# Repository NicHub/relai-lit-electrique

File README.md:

**Relai pour lit électrique**
=============================

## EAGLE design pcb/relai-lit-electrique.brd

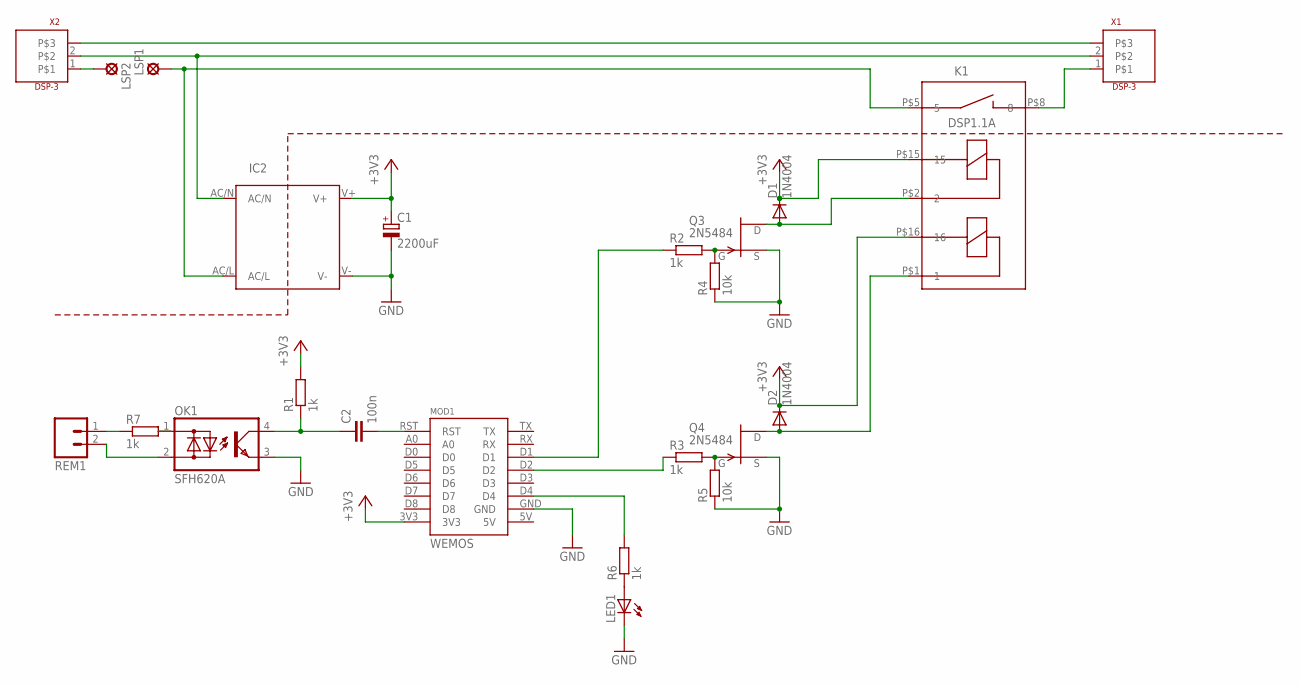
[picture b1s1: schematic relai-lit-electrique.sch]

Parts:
C1: 2200uF; E3,5-10
C2: 100n; C025-024X044
D1, D2: 1N4004; DO41-10
IC2: IRM_03
K1: DSP1.1A; DSP1A
LED1: LED3MM
LSP1, LSP2: SE14
MOD1: WEMOS
OK1: SFH620A; DIL04
Q3, Q4: 2N5484; TO92-
R1, R2, R3, R6: 1k; 0204/7
R4, R5: 10k; 0204/7
R7: 1k; 0207/10
REM1: M025MM; SCREWTERMINAL-5MM-2
X1, X2: DSP-3; RND-CONNECT-3

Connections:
+3V3: C1.+, D1.C, D2.C, IC2.V+, K1.P$15 (15), K1.P$16 (16), MOD1.3V3, R1.2
GND: C1.-, IC2.V-, LED1.K (C), MOD1.GND, OK1.3 (E), Q3.2 (S), Q4.2 (S), R4.1, R5.1
MASSE: X1.3, X2.3
unnamed: Q3.1 (G), R2.2, R4.2
unnamed: Q4.1 (G), R3.2, R5.2
unnamed: D1.A, K1.P$2 (2), Q3.3 (D)
unnamed: MOD1.D4, R6.2
unnamed: C2.2, MOD1.RST
unnamed: D2.A, K1.P$1 (1), Q4.3 (D)
unnamed: C2.1, OK1.4 (C), R1.1
unnamed: K1.P$8 (8), X1.1
unnamed: R7.1, REM1.1
unnamed: LED1.A, R6.1
unnamed: OK1.1 (AC1), R7.2
unnamed: MOD1.D1, R2.1
unnamed: MOD1.D2, R3.1
unnamed: OK1.2 (AC2), REM1.2
NEUTRE: IC2.AC/N, X1.2, X2.2
PHASE: LSP2.MP, X2.1
PHASE_B: IC2.AC/L, K1.P$5 (5), LSP1.MP

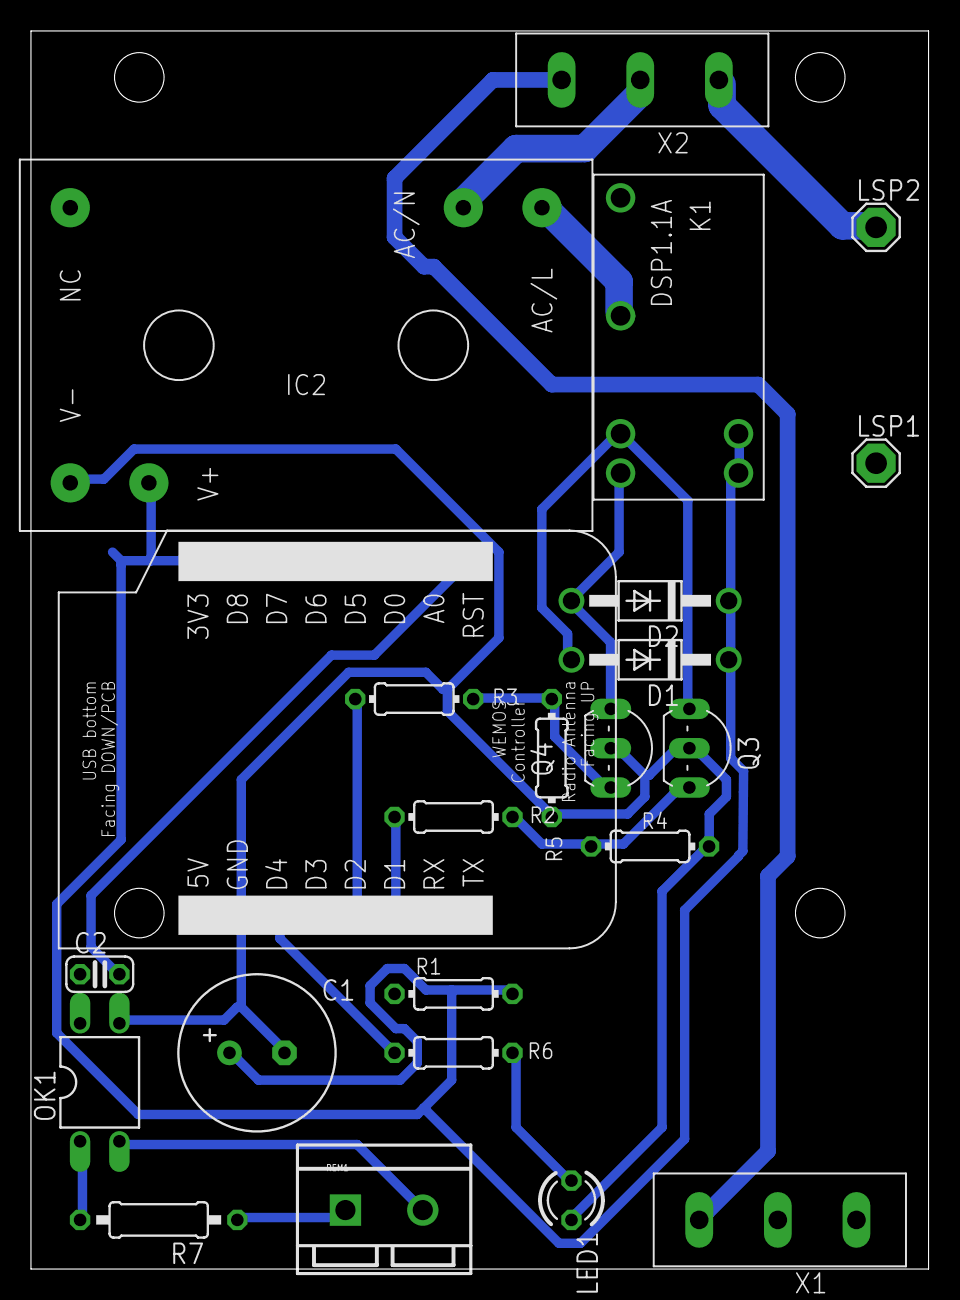
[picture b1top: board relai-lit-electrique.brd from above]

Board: 2 copper layers, 58.0 x 80.0 mm, 23 parts (0 on the bottom side), 20 nets.

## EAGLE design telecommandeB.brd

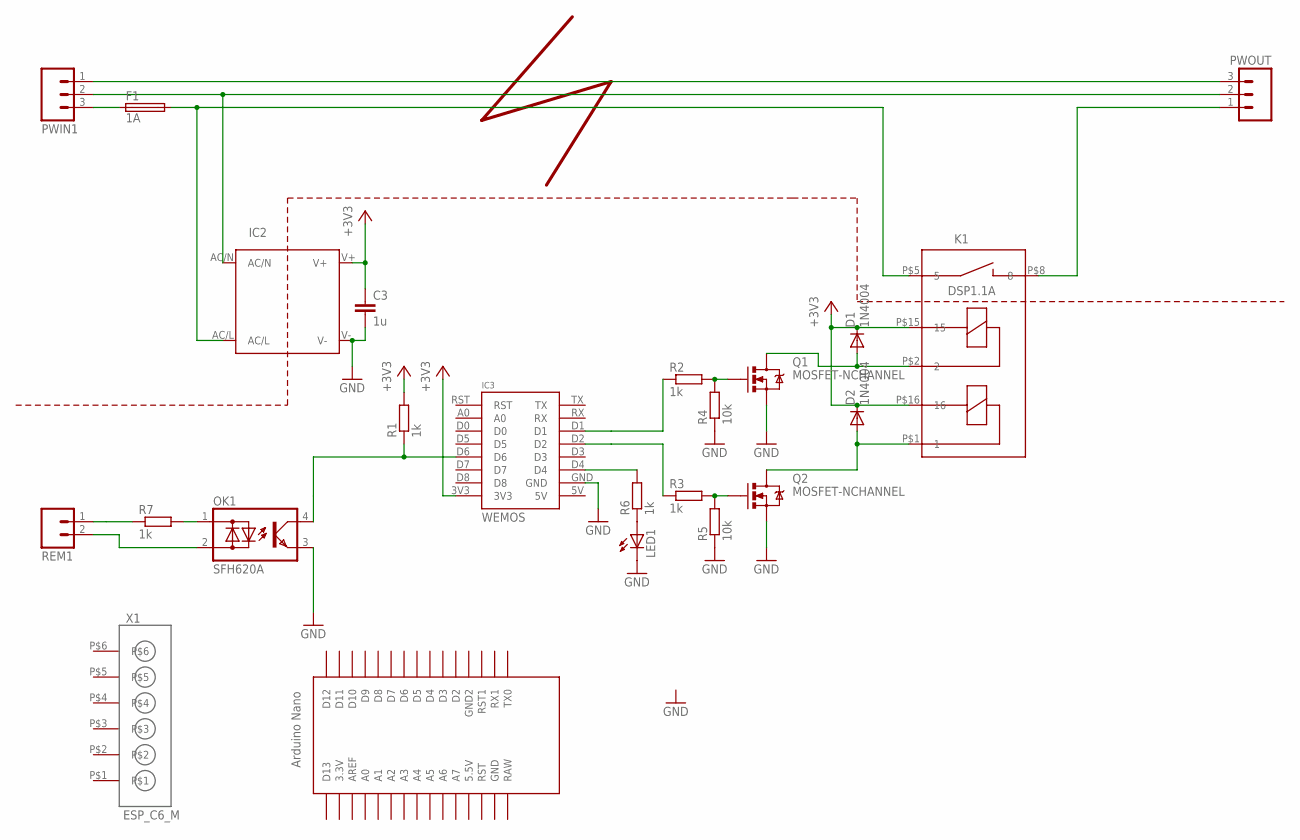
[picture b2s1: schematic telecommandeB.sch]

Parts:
C3: 1u; C025-024X044
D1, D2: 1N4004; DO41-10
F1: 1A; GSH15
IC2: IRM_03
IC3: WEMOS
K1: DSP1.1A; DSP1A
LED1: LED3MM
OK1: SFH620A; DIL04
PWIN1: M03-SCREW-5MM; SCREWTERMINAL-5MM-3
PWOUT: M03-SCREW-5MM; SCREWTERMINAL-5MM-3
Q1, Q2: MOSFET-NCHANNEL; TO-92-L
R1, R7: 1k; 0207/10
R2, R3, R6: 1k; 0204/7
R4, R5: 10k; 0204/7
REM1: M025MM; SCREWTERMINAL-5MM-2
U$1: NANO
X1: ESP_C6_M; ESP-CONNECT-6

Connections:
+3V3: C3.1, D1.C, D2.C, IC2.V+, IC3.3V3, K1.P$15 (15), K1.P$16 (16), R1.2
GND: C3.2, IC2.V-, IC3.GND, LED1.K (C), OK1.3 (E), Q1.P$1 (S), Q2.P$1 (S), R4.1, R5.1
MASSE: PWIN1.1, PWOUT.3
N: IC2.AC/N, PWIN1.2, PWOUT.2
unnamed: Q1.P$2 (G), R2.2, R4.2
unnamed: Q2.P$2 (G), R3.2, R5.2
unnamed: D1.A, K1.P$2 (2), Q1.P$3 (D)
unnamed: IC3.D4, R6.2
unnamed: D2.A, K1.P$1 (1), Q2.P$3 (D)
unnamed: K1.P$8 (8), PWOUT.1
unnamed: R7.1, REM1.1
unnamed: LED1.A, R6.1
unnamed: OK1.1 (AC1), R7.2
unnamed: IC3.D1, R2.1
unnamed: IC3.D2, R3.1
unnamed: OK1.2 (AC2), REM1.2
unnamed: IC3.D6, OK1.4 (C), R1.1
P: F1.2, IC2.AC/L, K1.P$5 (5)
PI: F1.1, PWIN1.3

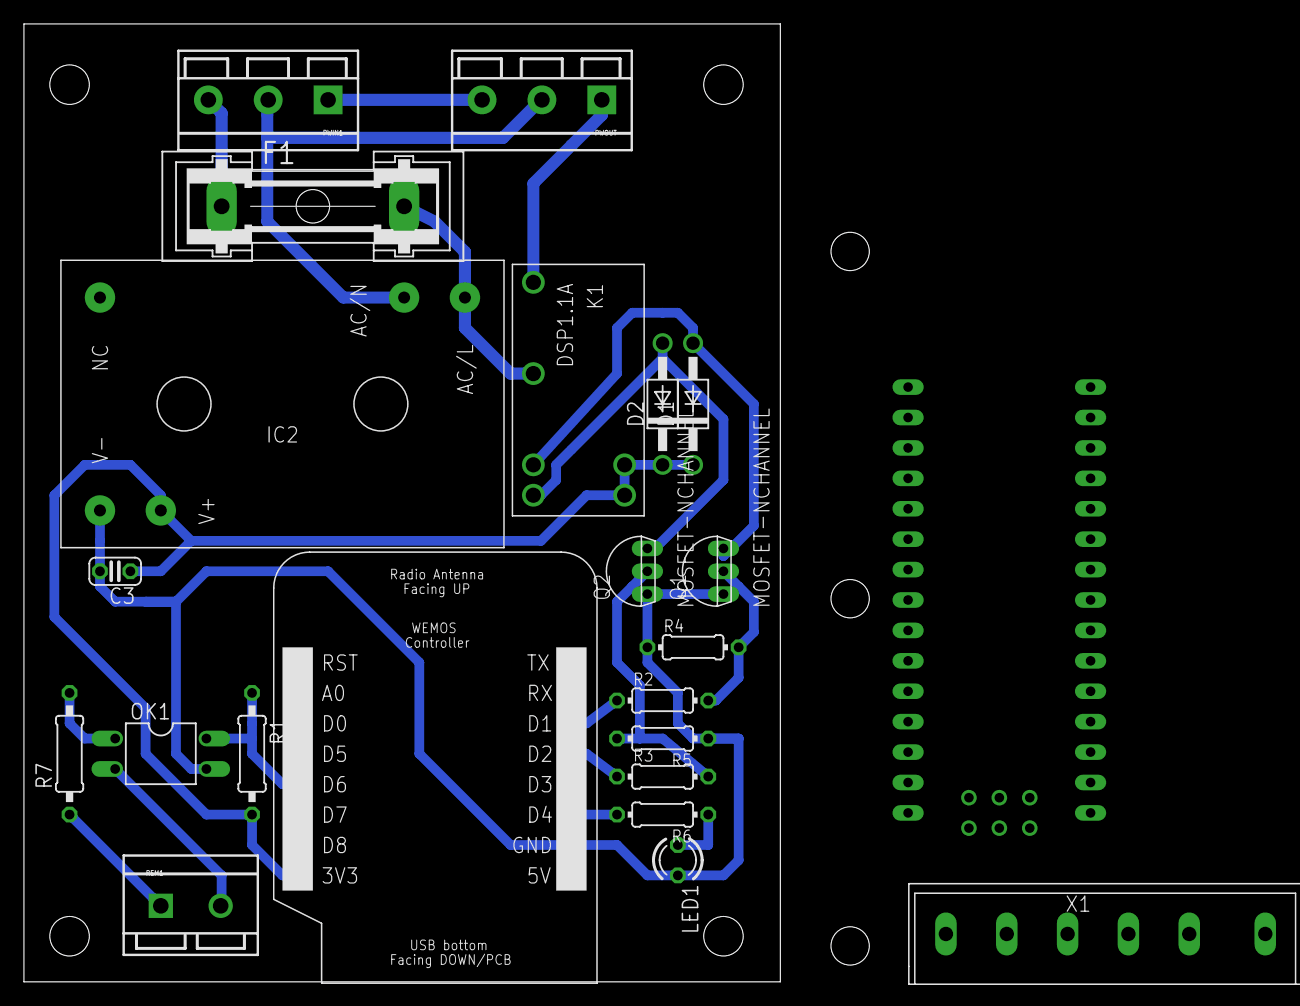
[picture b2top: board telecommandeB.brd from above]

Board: 2 copper layers, 63.2 x 80.0 mm, 23 parts (0 on the bottom side), 19 nets.

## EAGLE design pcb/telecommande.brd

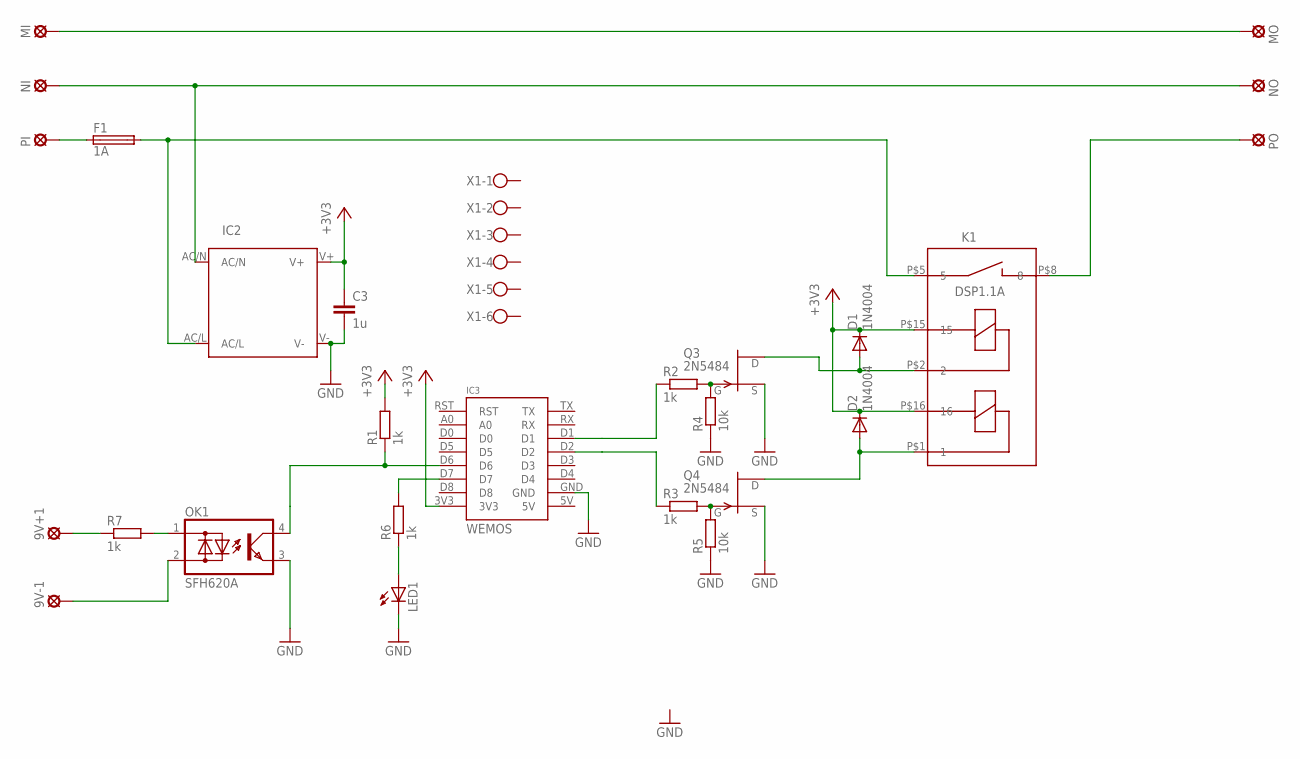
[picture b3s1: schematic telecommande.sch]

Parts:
9V+1, 9V-1: LSP13
C3: 1u; C025-024X044
D1, D2: 1N4004; DO41-10
F1: 1A; GSH15
IC2: IRM_03
IC3: WEMOS
K1: DSP1.1A; DSP1A
LED1: LED3MM
MI: LSP13
MO: LSP13
NI: LSP13
NO: LSP13
OK1: SFH620A; DIL04
PI: LSP13
PO: LSP13
Q3, Q4: 2N5484; TO92-
R1, R2, R3, R6, R7: 1k; 0207/10
R4, R5: 10k; 0207/10
X1: W237-6

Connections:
+3V3: C3.1, D1.C, D2.C, IC2.V+, IC3.3V3, K1.P$15 (15), K1.P$16 (16), R1.2
GND: C3.2, IC2.V-, IC3.GND, LED1.K (C), OK1.3 (E), Q3.2 (S), Q4.2 (S), R4.1, R5.1
MASSE: MI.MP, MO.MP
N: IC2.AC/N, NI.MP, NO.MP
unnamed: Q3.1 (G), R2.2, R4.2
unnamed: Q4.1 (G), R3.2, R5.2
unnamed: D1.A, K1.P$2 (2), Q3.3 (D)
unnamed: D2.A, K1.P$1 (1), Q4.3 (D)
unnamed: K1.P$8 (8), PO.MP
unnamed: 9V+1.MP, R7.1
unnamed: LED1.A, R6.1
unnamed: OK1.1 (AC1), R7.2
unnamed: IC3.D1, R2.1
unnamed: IC3.D2, R3.1
unnamed: IC3.D7, R6.2
unnamed: 9V-1.MP, OK1.2 (AC2)
unnamed: IC3.D6, OK1.4 (C), R1.1
P: F1.2, IC2.AC/L, K1.P$5 (5)
PI: F1.1, PI.MP

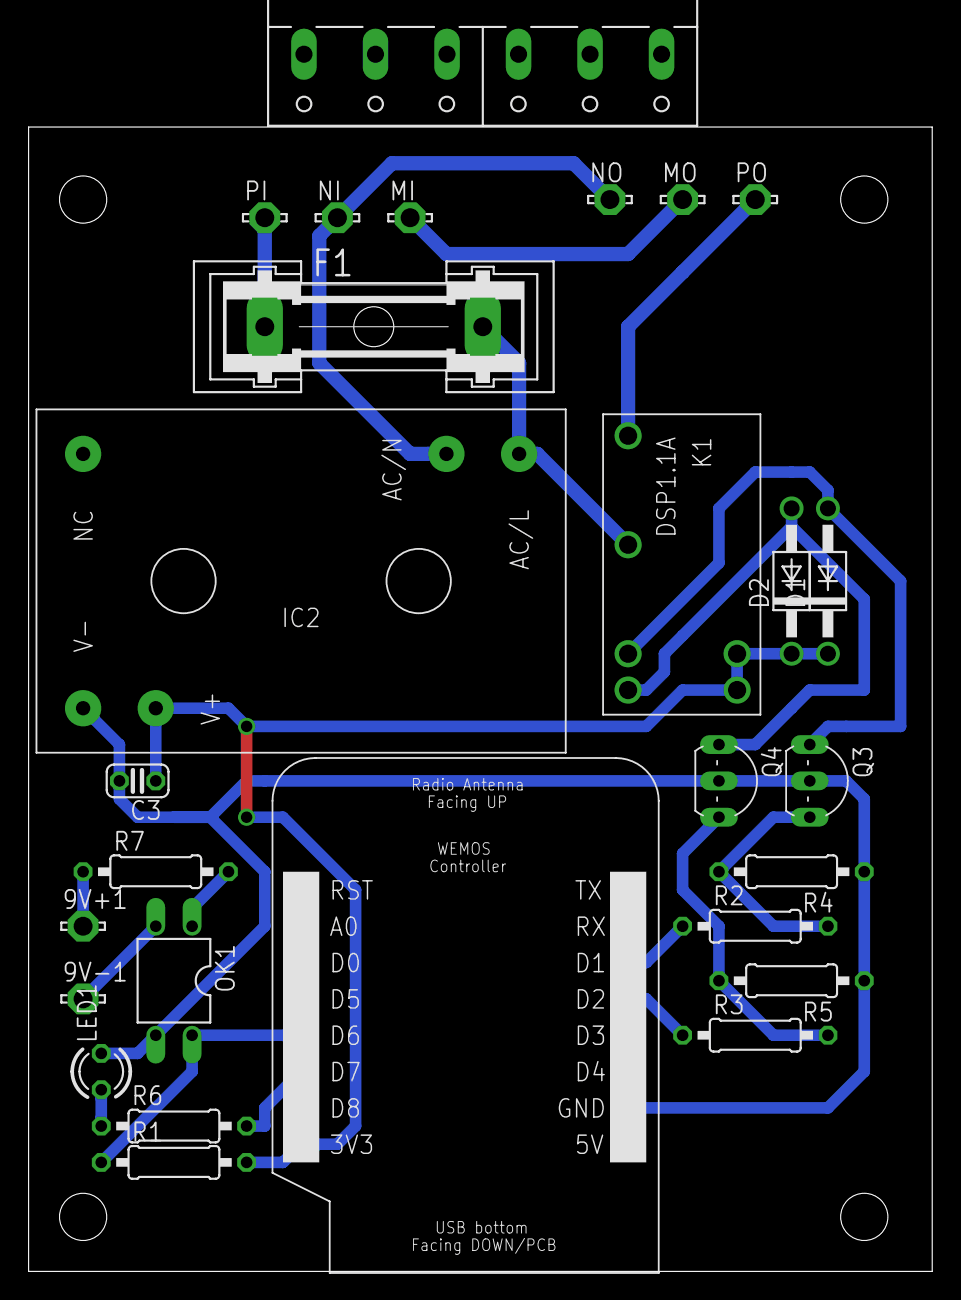
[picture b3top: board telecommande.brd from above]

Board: 2 copper layers, 63.2 x 80.0 mm, 27 parts (0 on the bottom side), 19 nets.

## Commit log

2017-03-02 cleanup
2017-03-03 ajout README
